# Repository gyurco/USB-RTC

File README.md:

An USB-RTC board for MiST, RPi, etc., based on Till Harbaum's [I2C-Tiny-USB](https://github.com/harbaum/I2C-Tiny-USB) project.

Further usage instructions:
https://github.com/mist-devel/mist-board/wiki/UsbRtc

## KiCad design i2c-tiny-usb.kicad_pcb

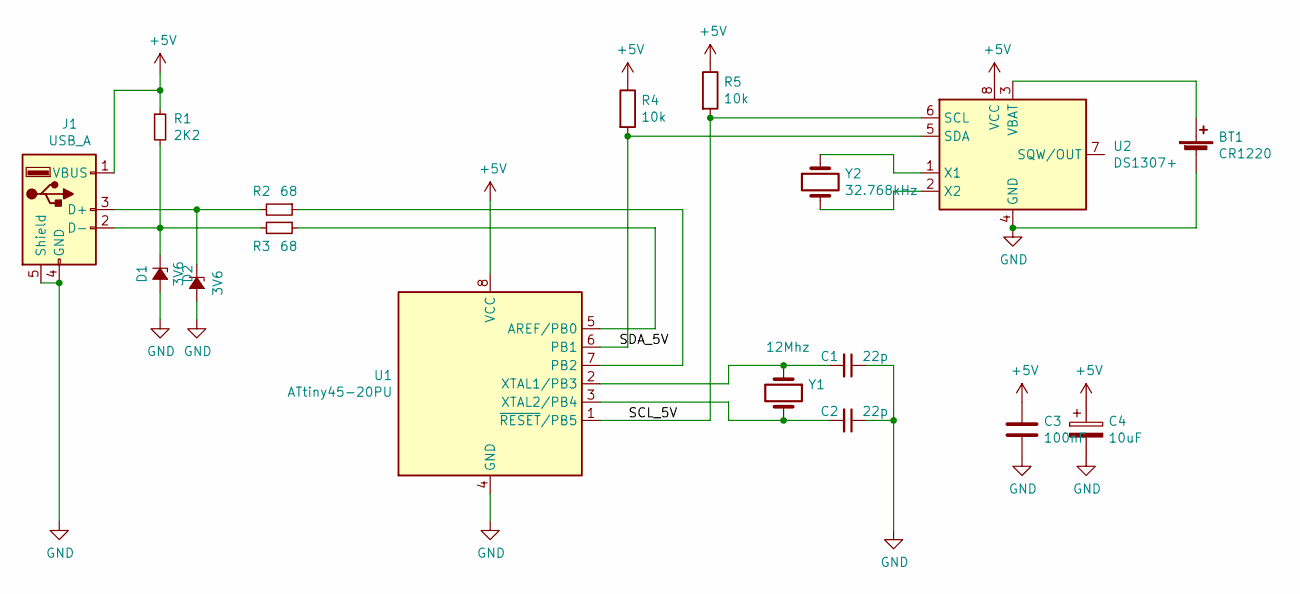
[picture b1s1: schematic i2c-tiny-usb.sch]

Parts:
BT1: CR1220; BatteryHolder_Keystone_500
C1, C2: 22p; C_1206_3216Metric_Pad1.42x1.75mm_HandSolder
C3: 100nF; C_1206_3216Metric_Pad1.42x1.75mm_HandSolder
C4: 10uF; CP_Radial_D5.0mm_P2.00mm
D1, D2: 3V6; D_1206_3216Metric_Pad1.42x1.75mm_HandSolder
J1: USB_A; USB_A_CNCTech_1001-011-01101_Horizontal
R1: 2K2; R_1206_3216Metric_Pad1.42x1.75mm_HandSolder
R2, R3: 68; R_1206_3216Metric_Pad1.42x1.75mm_HandSolder
R4, R5: 10k; R_1206_3216Metric_Pad1.42x1.75mm_HandSolder
U1: ATtiny45-20PU; SO-8_3.9x4.9mm_P1.27mm
U2: DS1307+; SO-8_3.9x4.9mm_P1.27mm
Y1: 12Mhz; Crystal_SMD_5032-2Pin_5.0x3.2mm_HandSoldering
Y2: 32.768kHz; Crystal_Round_D3.0mm_Vertical

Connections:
+5V: C3.1, C4.1, J1.1 (VBUS), R1.1, R4.1, R5.1, U1.8 (VCC), U2.8 (VCC)
/SCL_5V: R5.2, U1.1 (~RESET~/PB5), U2.6 (SCL)
/SDA_5V: R4.2, U1.6 (PB1), U2.5 (SDA)
GND: BT1.2 (-), C1.1, C2.1, C3.2, C4.2, D1.2 (A), D2.2 (A), J1.4 (GND), J1.5 (Shield), U1.4 (GND), U2.4 (GND)
unnamed: BT1.1 (+), U2.3 (VBAT)
unnamed: C1.2, U1.2 (XTAL1/PB3), Y1.1
unnamed: C2.2, U1.3 (XTAL2/PB4), Y1.2
unnamed: D1.1 (K), J1.2 (D-), R1.2, R3.2
unnamed: D2.1 (K), J1.3 (D+), R2.2
unnamed: R2.1, U1.7 (PB2)
unnamed: R3.1, U1.5 (AREF/PB0)
unnamed: U2.1 (X1), Y2.1
unnamed: U2.2 (X2), Y2.2

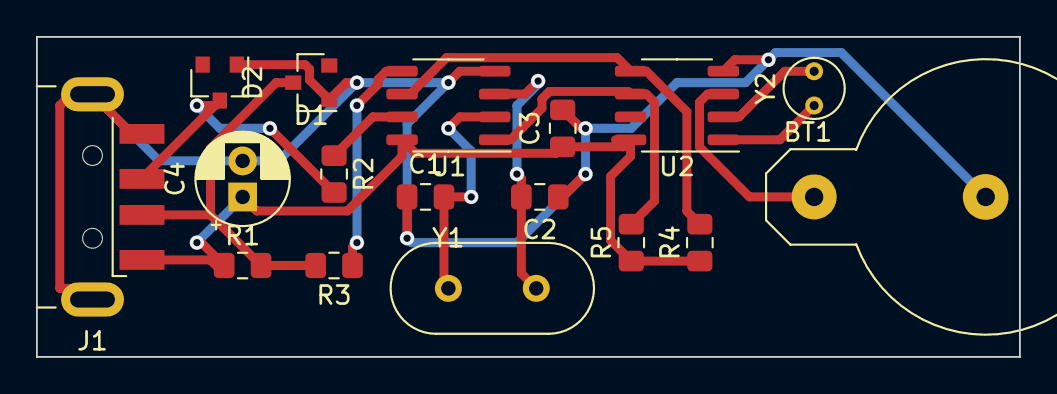
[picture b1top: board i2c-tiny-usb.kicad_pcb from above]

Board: 2 copper layers, 54.6 x 17.8 mm, 17 parts (0 on the bottom side), 13 nets.

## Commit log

2021-04-12 Add pic
